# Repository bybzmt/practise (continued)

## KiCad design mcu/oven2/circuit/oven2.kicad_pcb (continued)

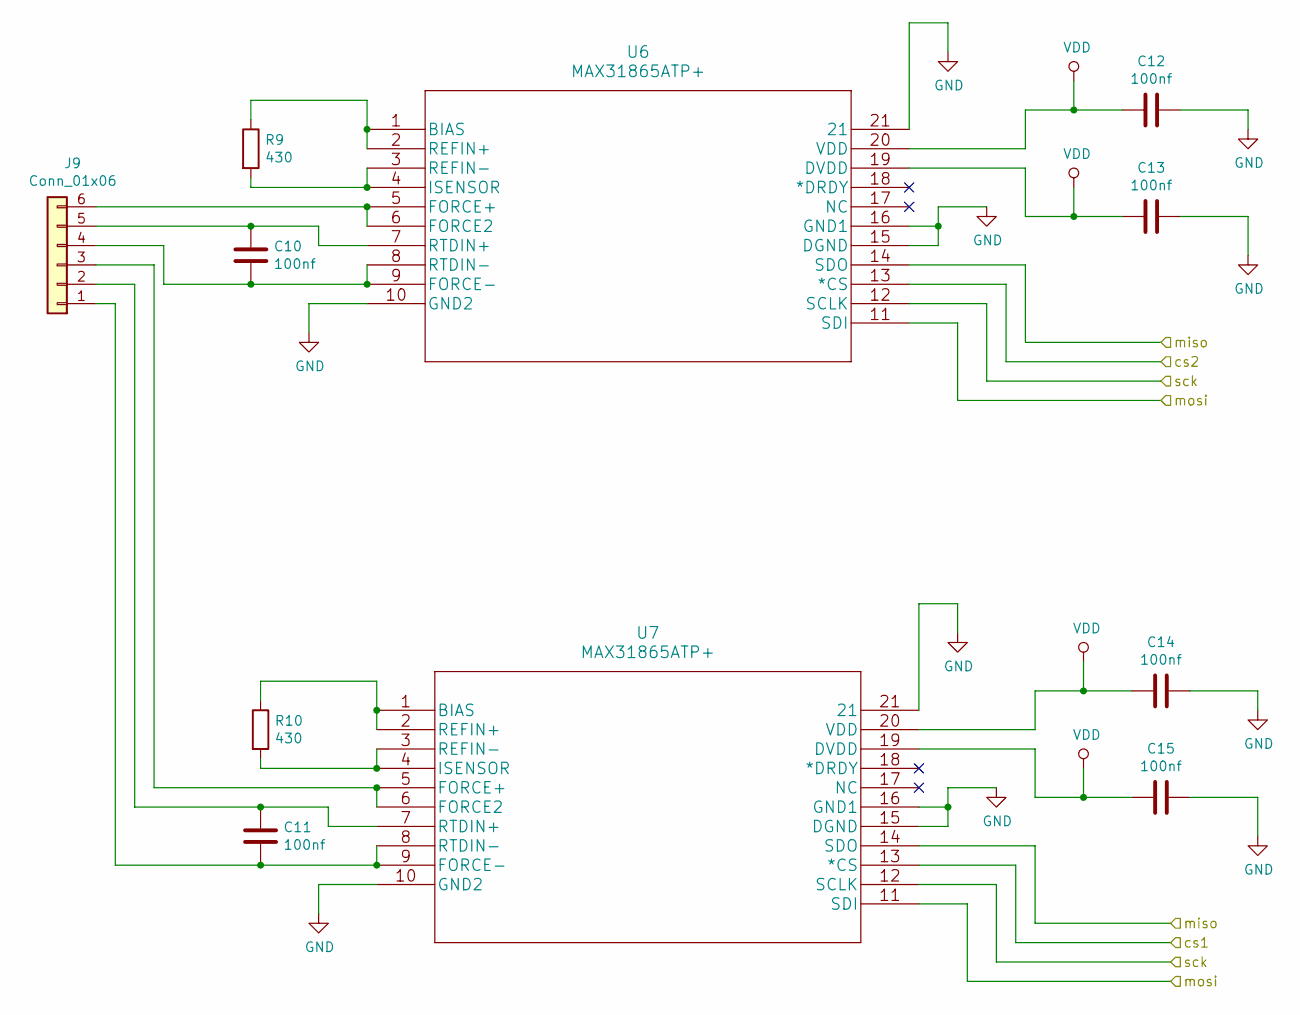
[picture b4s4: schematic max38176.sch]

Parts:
C10, C11, C12, C13, C14, C15: 100nf; C_0805_2012Metric
J9: Conn_01x06; PinSocket_1x06_P2.54mm_Vertical
R9, R10: 430; R_0805_2012Metric
U6, U7: MAX31865ATP+

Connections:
/cs1: U7.13 (*CS); also elsewhere on the board
/cs2: U6.13 (*CS); also elsewhere on the board
/miso: U6.14 (SDO), U7.14 (SDO); also elsewhere on the board
/mosi: U6.11 (SDI), U7.11 (SDI); also elsewhere on the board
/sck: U6.12 (SCLK), U7.12 (SCLK); also elsewhere on the board
GND: C12.1, C13.1, C14.1, C15.1, U6.10 (GND2), U6.15 (DGND), U6.16 (GND1), U6.21, U7.10 (GND2), U7.15 (DGND), U7.16 (GND1), U7.21; also elsewhere on the board
unnamed: C10.1, J9.5, U6.7 (RTDIN+)
unnamed: C10.2, J9.4, U6.8 (RTDIN-), U6.9 (FORCE-)
unnamed: C11.1, J9.2, U7.7 (RTDIN+)
unnamed: C11.2, J9.1, U7.8 (RTDIN-), U7.9 (FORCE-)
unnamed: J9.3, U7.5 (FORCE+), U7.6 (FORCE2)
unnamed: J9.6, U6.5 (FORCE+), U6.6 (FORCE2)
unnamed: R9.1, U6.1 (BIAS), U6.2 (REFIN+)
unnamed: R9.2, U6.3 (REFIN-), U6.4 (ISENSOR)
unnamed: R10.1, U7.1 (BIAS), U7.2 (REFIN+)
unnamed: R10.2, U7.3 (REFIN-), U7.4 (ISENSOR)
VDD: C12.2, C13.2, C14.2, C15.2, U6.19 (DVDD), U6.20 (VDD), U7.19 (DVDD), U7.20 (VDD); also elsewhere on the board

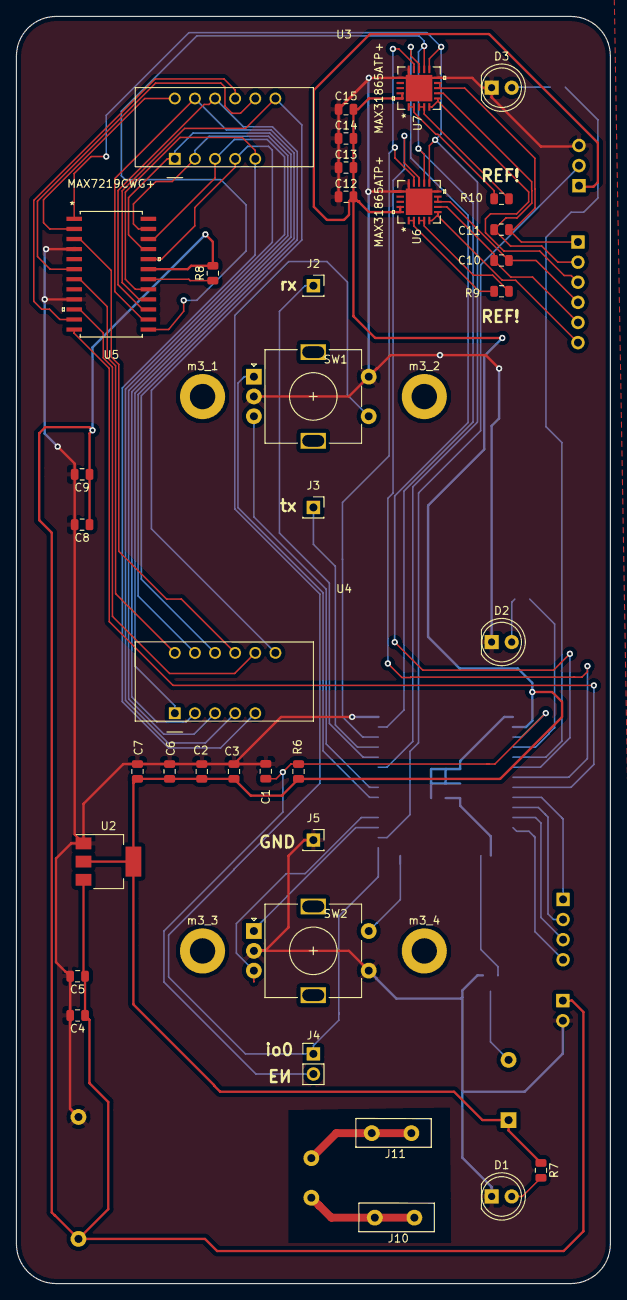
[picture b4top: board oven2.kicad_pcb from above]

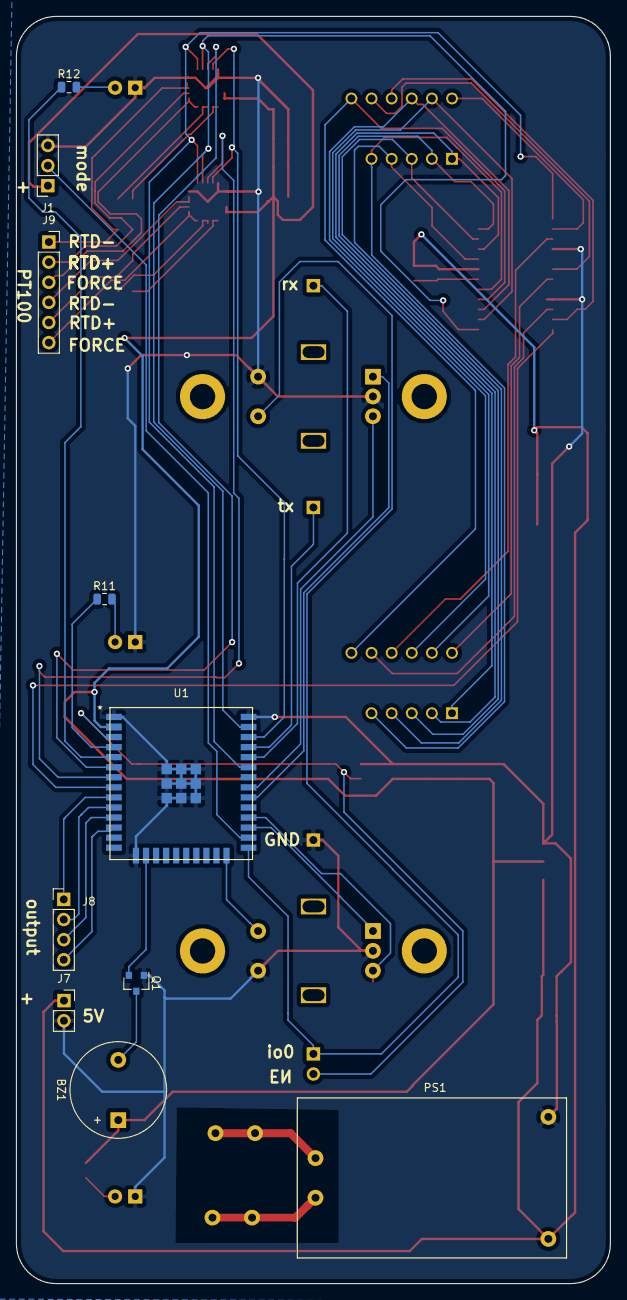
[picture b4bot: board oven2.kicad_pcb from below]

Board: 2 copper layers, 75.0 x 160.0 mm, 51 parts (10 on the bottom side), 57 nets.

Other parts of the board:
m3_1, m3_2, m3_3, m3_4: M3; MountingHole_3.2mm_M3_ISO7380_Pad

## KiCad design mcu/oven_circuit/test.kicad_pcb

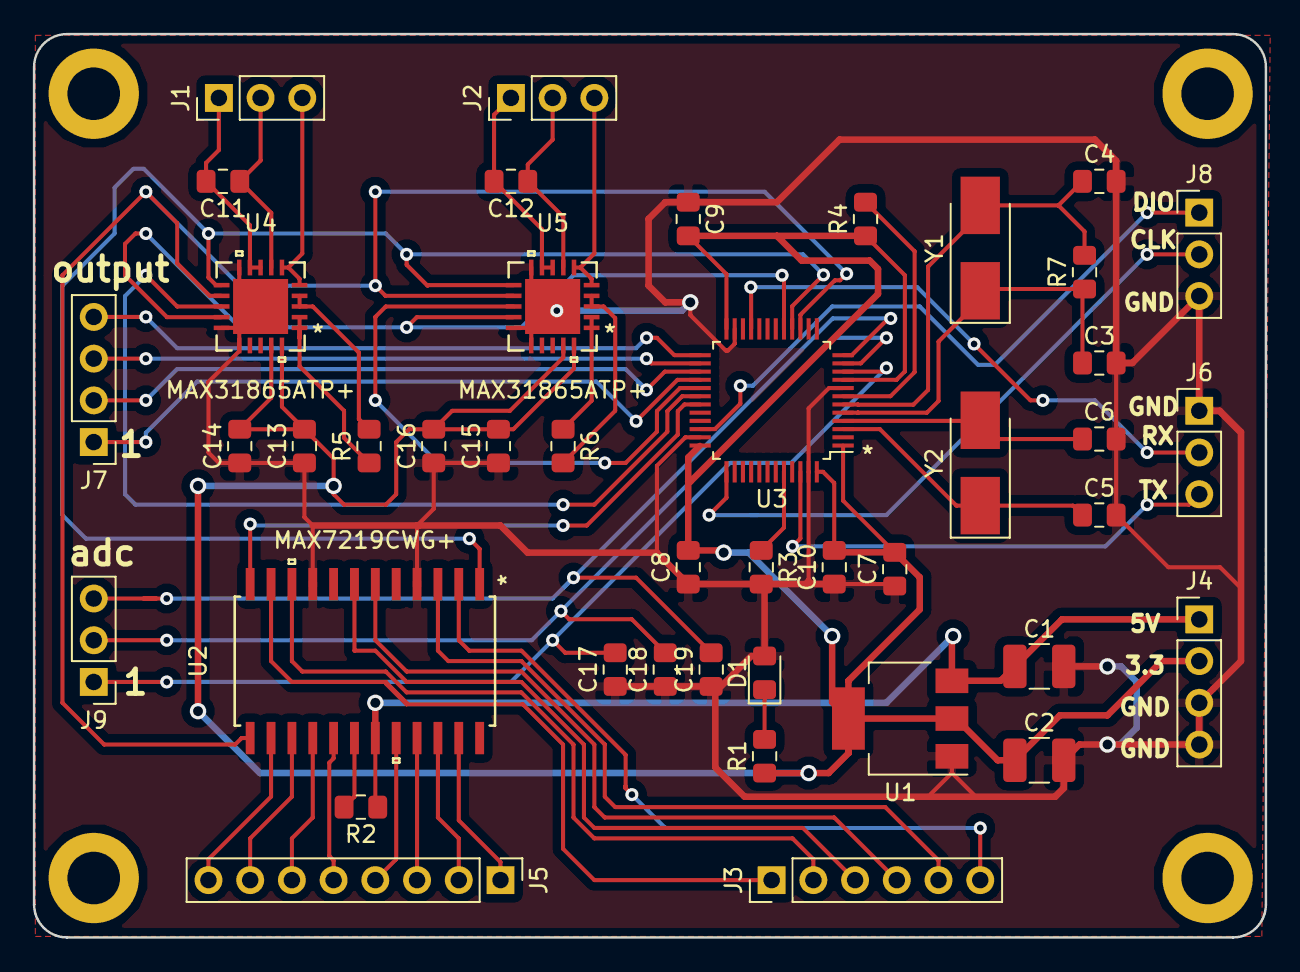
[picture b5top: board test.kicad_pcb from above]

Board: 2 copper layers, 75.0 x 55.0 mm, 43 parts (0 on the bottom side), 52 nets.

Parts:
C1, C2: 10uf; C_1210_3225Metric_Pad1.42x2.65mm_HandSolder
C3, C4: 22pf; C_0805_2012Metric_Pad1.15x1.40mm_HandSolder
C5, C6: 12pf; C_0805_2012Metric_Pad1.15x1.40mm_HandSolder
C7, C8, C9, C10, C11, C12, C13, C14, C15, C16: 100nf; C_0805_2012Metric_Pad1.15x1.40mm_HandSolder
C17, C18, C19: 10nf; C_0805_2012Metric_Pad1.15x1.40mm_HandSolder
D1: LED; LED_0805_2012Metric_Pad1.15x1.40mm_HandSolder
J1: temperature_1; PinHeader_1x03_P2.54mm_Vertical
J2: temperature_2; PinHeader_1x03_P2.54mm_Vertical
J3: DIG_0_6; PinHeader_1x06_P2.54mm_Vertical
J4: power; PinHeader_1x04_P2.54mm_Vertical
J5: SEG; PinHeader_1x08_P2.54mm_Vertical
J6: usart; PinHeader_1x03_P2.54mm_Vertical
J7: output; PinHeader_1x04_P2.54mm_Vertical
J8: swd; PinHeader_1x03_P2.54mm_Vertical
J9: adc; PinHeader_1x03_P2.54mm_Vertical
R1: 1k; R_0805_2012Metric_Pad1.15x1.40mm_HandSolder
R2: 9.53k; R_0805_2012Metric_Pad1.15x1.40mm_HandSolder
R3, R4: 10k; R_0805_2012Metric_Pad1.15x1.40mm_HandSolder
R5, R6: 430; R_0805_2012Metric_Pad1.15x1.40mm_HandSolder
R7: 1m; R_0805_2012Metric_Pad1.15x1.40mm_HandSolder
U1: AMS1117-3.3; SOT-223-3_TabPin2
U2: MAX7219CWG+
U3: STM32F103C8Tx; STM32F103C8T6
U4, U5: MAX31865ATP+
Y1: 8m; Crystal_SMD_5032-2Pin_5.0x3.2mm_HandSoldering
Y2: 32.768; Crystal_SMD_5032-2Pin_5.0x3.2mm_HandSoldering

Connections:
/OSC32_IN: C5.1, U3.3, Y2.1
/OSC32_OUT: C6.1, U3.4, Y2.2
/Sheet5DA16D7E/force1: J1.3, U4.5, U4.6
/Sheet5DA16D7E/force2: J2.3, U5.5, U5.6
/Sheet5DA16D7E/rtdin1+: C11.1, J1.2, U4.7
/Sheet5DA16D7E/rtdin1-: C11.2, J1.1, U4.8, U4.9
/Sheet5DA16D7E/rtdin2+: C12.1, J2.2, U5.7
/Sheet5DA16D7E/rtdin2-: C12.2, J2.1, U5.8, U5.9
/XTAL_IN: C3.1, R7.1, U3.5, Y1.1
/XTAL_OUT: C4.1, R7.2, U3.6, Y1.2
/cs1: U3.29, U5.13
/cs2: U3.30, U4.13
/cs3: U2.12, U3.31
/miso: U3.17, U4.14, U5.14
/mosi: U2.1, U3.16, U4.11, U5.11
/sck: U2.13, U3.15, U4.12, U5.12
GND: C1.2, C2.2, C3.2, C4.2, C5.2, C6.2, C7.1, C8.1, C9.1, C10.1, C13.1, C14.1, C15.1, C16.1, C17.1, C18.1, C19.1, D1.2, J4.3, J4.4, J6.1, J8.3, R3.2, U1.1, U2.4, U2.9, U3.8, U3.23, U3.35, U3.47, U4.10, U4.15, U4.16, U4.21, U5.10, U5.15, U5.16, U5.21
unnamed: C17.2, J9.1, U3.10
unnamed: C18.2, J9.2, U3.11
unnamed: C19.2, J9.3, U3.12
unnamed: D1.1, R1.2
unnamed: J3.1, U2.11
unnamed: J3.2, U2.10
unnamed: J3.3, U2.7
unnamed: J3.4, U2.6
unnamed: J3.5, U2.3
unnamed: J3.6, U2.2
unnamed: J5.1, U2.23
unnamed: J5.2, U2.22
unnamed: J5.3, U2.21
unnamed: J5.4, U2.20
unnamed: J5.5, U2.17
unnamed: J5.6, U2.16
unnamed: J5.7, U2.15
unnamed: J5.8, U2.14
unnamed: J6.2, U3.21
unnamed: J6.3, U3.46
unnamed: J7.1, U3.28
unnamed: J7.2, U3.27
unnamed: J7.3, U3.26
unnamed: J7.4, U3.25
unnamed: J8.1, U3.34
unnamed: J8.2, U3.37
unnamed: R2.2, U2.18
unnamed: R3.1, U3.44
unnamed: R4.2, U3.7
unnamed: R5.1, U4.1, U4.2
unnamed: R5.2, U4.3, U4.4
unnamed: R6.1, U5.1, U5.2
unnamed: R6.2, U5.3, U5.4
VCC: C1.1, J4.1, R2.1, U1.3, U2.19
VDD: C2.1, C7.2, C8.2, C9.2, C10.2, C13.2, C14.2, C15.2, C16.2, J4.2, R1.1, R4.1, U1.2, U3.1, U3.9, U3.24, U3.36, U3.48, U4.19, U4.20, U5.19, U5.20

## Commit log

2019-08-05 cairo
2019-08-12 epoll
2019-08-12 readme
2019-09-18 tick mode
2019-09-18 use hspi
2019-09-24 adc ok
2019-09-29 24l01 test
2019-10-25 circuit
2019-11-10 电路板调试ok
2019-11-11 发酵以最高温度为准
2019-12-04 oven2
2019-12-04 move
2020-03-15 btree-kv
2020-03-15 gitignore
2020-03-18 btree
2020-03-19 can run
2020-03-19 test ok
2020-03-20 test
2020-03-21 locker
2020-06-18 digital-amplifier
2020-06-28 work ok
2020-06-28 makefile优化
2020-06-29 vol ok
2020-06-29 remove lock file
2020-10-26 stm32f446-usbaudio-test
2020-10-26 good++
2020-10-26 test2
2020-11-15 usb lib2 ok
2020-11-15 rm test2
2020-11-15 move file
2020-11-17 sai in test
2020-11-26 init
2020-12-01 pcb ok
2020-12-22 out_v1
2021-01-23 save
2021-02-05 play ok
2021-02-07 cpu copy ok
2021-02-09 tas6424 Reporting
2021-02-10 spdif
2021-02-11 spdif work
2021-02-13 work
2021-02-16 usb audio volmue
2021-02-19 spdif sync
2021-02-28 headphone
2021-03-11 IWDG
2021-03-12 spdif_on_event
2021-04-10 digital-amplifier2-v3
2021-04-13 main_v4
2021-04-19 ciruit_save
2021-04-23 mclk
2021-04-30 v4 usb work
2021-06-28 digital-amplifier2_v8
2021-07-08 amplifier2_v9
2021-07-18 digital-amplifier2_v10
2021-07-29 oled
2021-07-29 bt_spdif
2021-07-29 settings
2021-07-29 usb power
2021-07-30 bkpsram
2021-08-01 bak vol
2021-08-02 shell
2021-08-02 rm old
2021-08-18 pcm1792 De-Emphasis
2021-08-18 MS621FE
2021-08-26 1792
2021-12-09 ssr-svelte
2021-12-15 router
2022-01-22 Bump nanoid from 3.1.30 to 3.2.0 in /js/my-svelte-app
    Bumps [nanoid](https://github.com/ai/nanoid) from 3.1.30 to 3.2.0.
    - [Release notes](https://github.com/ai/nanoid/releases)
    - [Changelog](https://github.com/ai/nanoid/blob/main/CHANGELOG.md)
    - [Commits](https://github.com/ai/nanoid/compare/3.1.30...3.2.0)
    ---
    updated-dependencies:
2022-01-23 go example
2022-02-15 Bump follow-redirects from 1.14.7 to 1.14.8 in /js/my-svelte-app
    Bumps [follow-redirects](https://github.com/follow-redirects/follow-redirects) from 1.14.7 to 1.14.8.
    - [Release notes](https://github.com/follow-redirects/follow-redirects/releases)
    - [Commits](https://github.com/follow-redirects/follow-redirects/compare/v1.14.7...v1.14.8)
    ---
    updated-dependencies:
    - dependency-name: follow-redirects
2022-02-21 go mod
2022-02-21 Bump nanoid from 3.1.30 to 3.3.1 in /js/my-vue-app
    Bumps [nanoid](https://github.com/ai/nanoid) from 3.1.30 to 3.3.1.
    - [Release notes](https://github.com/ai/nanoid/releases)
    - [Changelog](https://github.com/ai/nanoid/blob/main/CHANGELOG.md)
    - [Commits](https://github.com/ai/nanoid/compare/3.1.30...3.3.1)
    ---
    updated-dependencies:
2022-02-21 Bump node-fetch from 2.6.6 to 2.6.7 in /js/my-vue-app
    Bumps [node-fetch](https://github.com/node-fetch/node-fetch) from 2.6.6 to 2.6.7.
    - [Release notes](https://github.com/node-fetch/node-fetch/releases)
    - [Commits](https://github.com/node-fetch/node-fetch/compare/v2.6.6...v2.6.7)
    ---
    updated-dependencies:
    - dependency-name: node-fetch
2022-03-01 demo
2022-03-31 Bump minimist from 1.2.5 to 1.2.6 in /js/my-vue-app
    Bumps [minimist](https://github.com/substack/minimist) from 1.2.5 to 1.2.6.
    - [Release notes](https://github.com/substack/minimist/releases)
    - [Commits](https://github.com/substack/minimist/compare/1.2.5...1.2.6)
    ---
    updated-dependencies:
    - dependency-name: minimist
2022-03-31 Bump minimist from 1.2.5 to 1.2.6 in /js/my-svelte-app
    Bumps [minimist](https://github.com/substack/minimist) from 1.2.5 to 1.2.6.
    - [Release notes](https://github.com/substack/minimist/releases)
    - [Commits](https://github.com/substack/minimist/compare/1.2.5...1.2.6)
    ---
    updated-dependencies:
    - dependency-name: minimist
2022-05-21 Bump nanoid from 3.1.30 to 3.3.4 in /js/my-vue-app
    Bumps [nanoid](https://github.com/ai/nanoid) from 3.1.30 to 3.3.4.
    - [Release notes](https://github.com/ai/nanoid/releases)
    - [Changelog](https://github.com/ai/nanoid/blob/main/CHANGELOG.md)
    - [Commits](https://github.com/ai/nanoid/compare/3.1.30...3.3.4)
    ---
    updated-dependencies:
2022-06-09 tmp socks
2022-06-13 move to /bybzmt/sshProxy
2022-07-15 Bump svelte from 3.44.2 to 3.49.0 in /js/my-svelte-app
    Bumps [svelte](https://github.com/sveltejs/svelte) from 3.44.2 to 3.49.0.
    - [Release notes](https://github.com/sveltejs/svelte/releases)
    - [Changelog](https://github.com/sveltejs/svelte/blob/master/CHANGELOG.md)
    - [Commits](https://github.com/sveltejs/svelte/compare/v3.44.2...v3.49.0)
    ---
    updated-dependencies:
2022-08-30 Bump vite from 2.6.14 to 2.9.13 in /js/my-vue-app
    Bumps [vite](https://github.com/vitejs/vite/tree/HEAD/packages/vite) from 2.6.14 to 2.9.13.
    - [Release notes](https://github.com/vitejs/vite/releases)
    - [Changelog](https://github.com/vitejs/vite/blob/main/packages/vite/CHANGELOG.md)
    - [Commits](https://github.com/vitejs/vite/commits/v2.9.13/packages/vite)
    ---
    updated-dependencies:
2022-08-30 Bump vite from 2.7.12 to 2.9.13 in /js/my-svelte-app
    Bumps [vite](https://github.com/vitejs/vite/tree/HEAD/packages/vite) from 2.7.12 to 2.9.13.
    - [Release notes](https://github.com/vitejs/vite/releases)
    - [Changelog](https://github.com/vitejs/vite/blob/main/packages/vite/CHANGELOG.md)
    - [Commits](https://github.com/vitejs/vite/commits/v2.9.13/packages/vite)
    ---
    updated-dependencies:
2022-11-12 Bump minimatch from 3.0.4 to 3.0.8 in /js/my-svelte-app
    Bumps [minimatch](https://github.com/isaacs/minimatch) from 3.0.4 to 3.0.8.
    - [Release notes](https://github.com/isaacs/minimatch/releases)
    - [Commits](https://github.com/isaacs/minimatch/compare/v3.0.4...v3.0.8)
    ---
    updated-dependencies:
    - dependency-name: minimatch
2022-12-07 Bump qs and express in /js/my-svelte-app
    Bumps [qs](https://github.com/ljharb/qs) to 6.11.0 and updates ancestor dependency [express](https://github.com/expressjs/express). These dependencies need to be updated together.
    Updates `qs` from 6.9.6 to 6.11.0
    - [Release notes](https://github.com/ljharb/qs/releases)
    - [Changelog](https://github.com/ljharb/qs/blob/main/CHANGELOG.md)
    - [Commits](https://github.com/ljharb/qs/compare/v6.9.6...v6.11.0)
    Updates `express` from 4.17.2 to 4.18.2
2022-12-08 Bump qs and express in /js/my-vue-app
    Bumps [qs](https://github.com/ljharb/qs) to 6.11.0 and updates ancestor dependency [express](https://github.com/expressjs/express). These dependencies need to be updated together.
    Updates `qs` from 6.7.0 to 6.11.0
    - [Release notes](https://github.com/ljharb/qs/releases)
    - [Changelog](https://github.com/ljharb/qs/blob/main/CHANGELOG.md)
    - [Commits](https://github.com/ljharb/qs/compare/v6.7.0...v6.11.0)
    Updates `express` from 4.17.1 to 4.18.2
2022-12-14 Bump express from 4.17.1 to 4.17.3 in /js/my-vue-app
    Bumps [express](https://github.com/expressjs/express) from 4.17.1 to 4.17.3.
    - [Release notes](https://github.com/expressjs/express/releases)
    - [Changelog](https://github.com/expressjs/express/blob/master/History.md)
    - [Commits](https://github.com/expressjs/express/compare/4.17.1...4.17.3)
    ---
    updated-dependencies:
2022-12-15 Bump express from 4.17.2 to 4.17.3 in /js/my-svelte-app
    Bumps [express](https://github.com/expressjs/express) from 4.17.2 to 4.17.3.
    - [Release notes](https://github.com/expressjs/express/releases)
    - [Changelog](https://github.com/expressjs/express/blob/master/History.md)
    - [Commits](https://github.com/expressjs/express/compare/4.17.2...4.17.3)
    ---
    updated-dependencies:
2023-01-07 Bump json5 from 2.2.0 to 2.2.3 in /js/my-vue-app
    Bumps [json5](https://github.com/json5/json5) from 2.2.0 to 2.2.3.
    - [Release notes](https://github.com/json5/json5/releases)
    - [Changelog](https://github.com/json5/json5/blob/main/CHANGELOG.md)
    - [Commits](https://github.com/json5/json5/compare/v2.2.0...v2.2.3)
    ---
    updated-dependencies:
2023-03-06 Bump minimist from 1.2.5 to 1.2.8 in /js/my-vue-app
    Bumps [minimist](https://github.com/minimistjs/minimist) from 1.2.5 to 1.2.8.
    - [Release notes](https://github.com/minimistjs/minimist/releases)
    - [Changelog](https://github.com/minimistjs/minimist/blob/main/CHANGELOG.md)
    - [Commits](https://github.com/minimistjs/minimist/compare/v1.2.5...v1.2.8)
    ---
    updated-dependencies:
